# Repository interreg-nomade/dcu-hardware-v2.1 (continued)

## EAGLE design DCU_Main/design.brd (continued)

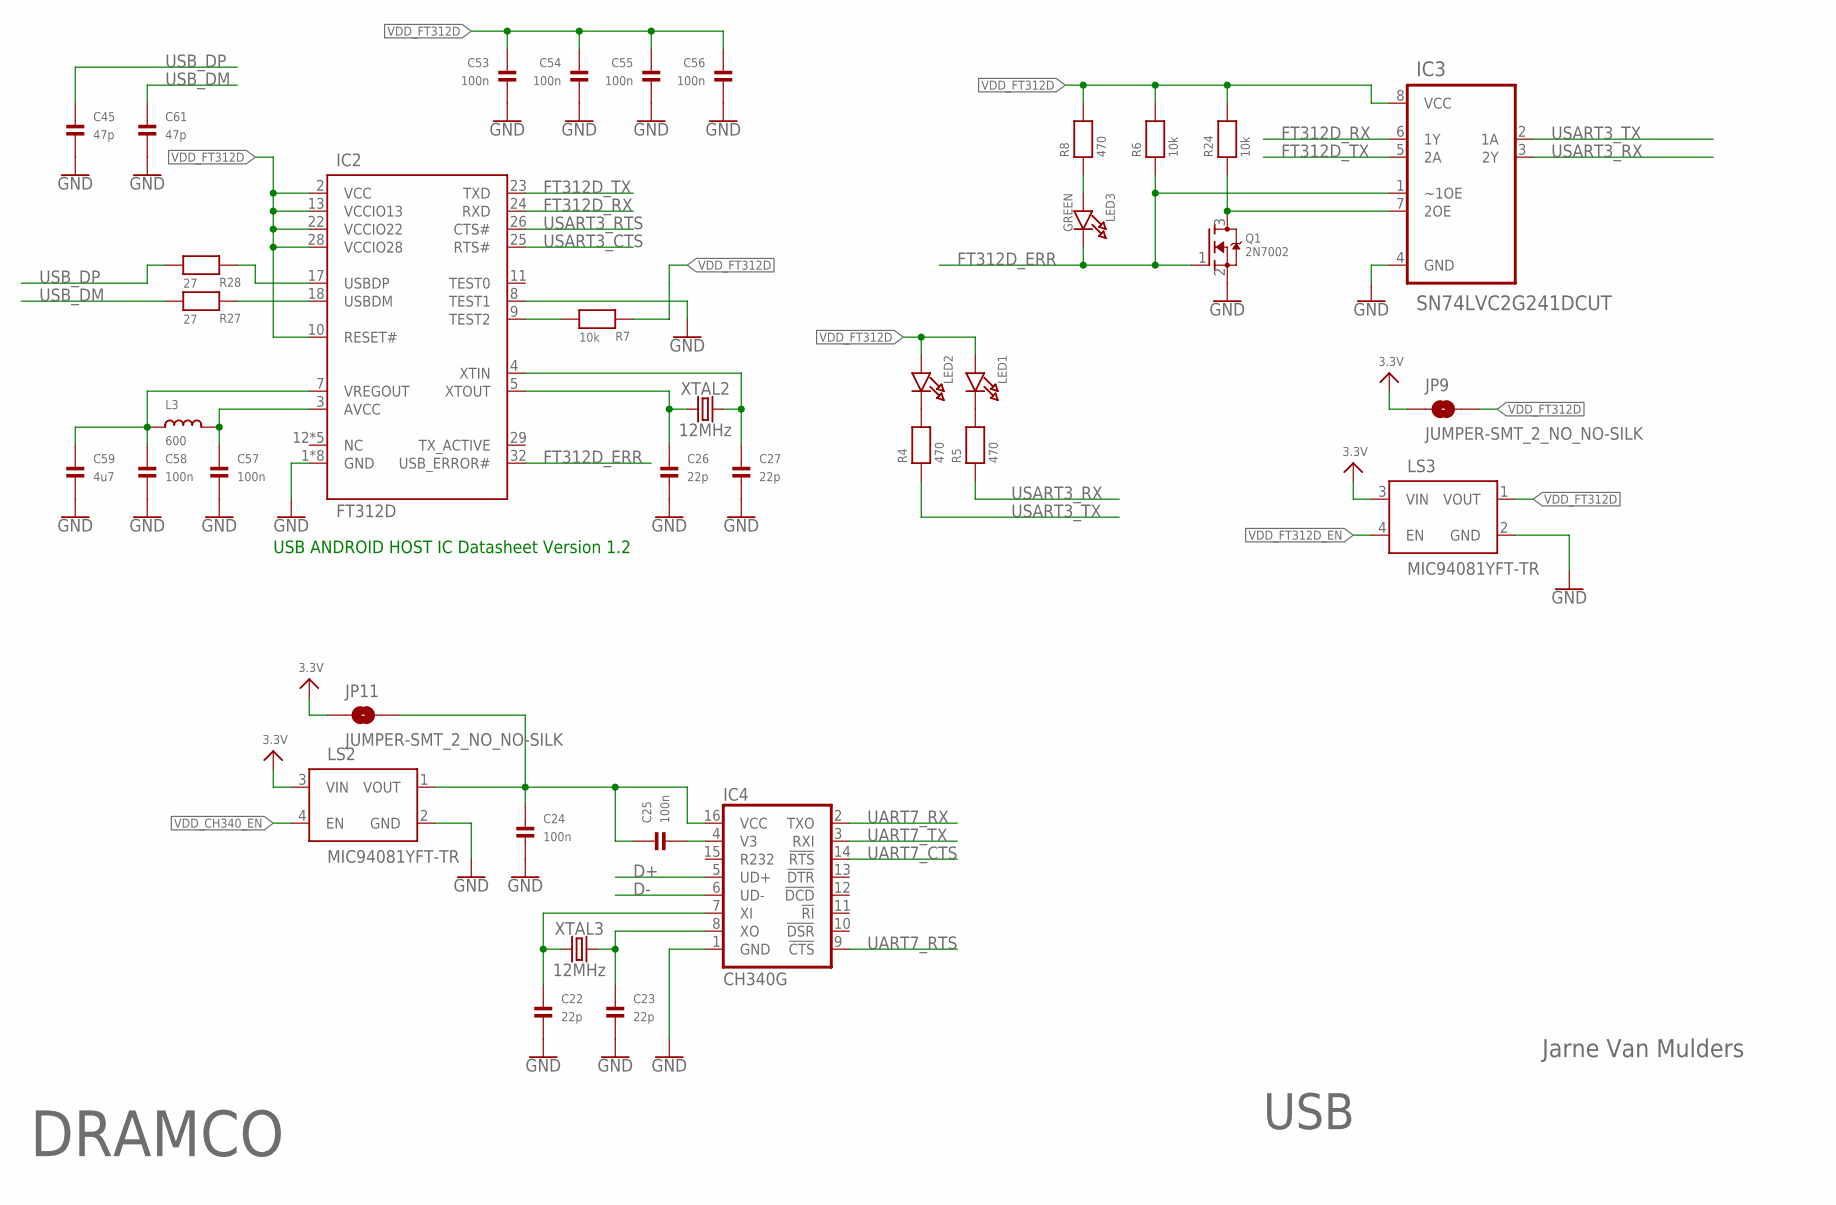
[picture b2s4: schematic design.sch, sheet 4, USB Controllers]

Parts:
C22, C23, C26, C27: 22p; 0603
C24, C25, C53, C54, C55, C56, C57, C58: 100n; 0603
C45, C61: 47p; 0603
C59: 4u7; 0603
IC2: FT312D; QFP80P900X900X160-32N
IC3: SN74LVC2G241DCUT; SOP50P310X90-8N
IC4: CH340G; SO016
JP9, JP11: JUMPER-SMT_2_NO_NO-SILK; SMT-JUMPER_2_NO_NO-SILK
L3: 600; 0603
LED1, LED2: LED0805; CHIPLED_0805
LED3: GREEN; CHIPLED_0805
LS2, LS3: MIC94081YFT-TR; IC_MIC94081YFT-TR
Q1: 2N7002; SOT23-WIDE
R4, R5, R8: 470; 0603
R6, R7, R24: 10k; 0603
R27, R28: 27; 0603
XTAL2, XTAL3: 12MHz; CRYSTAL-SMD-3.2X2.5MM

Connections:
3.3V: JP9.1, JP11.1, LS2.3 (VIN), LS3.3 (VIN); also elsewhere on the board
D+: IC4.5 (UD+); also elsewhere on the board
D-: IC4.6 (UD-); also elsewhere on the board
FT312D_ERR: IC2.32 (USB_ERROR#), IC3.1 (~1OE), LED3.C, Q1.1 (G), R6.1; also elsewhere on the board
FT312D_RX: IC2.24 (RXD), IC3.6 (1Y)
FT312D_TX: IC2.23 (TXD), IC3.5 (2A)
GND: C22.2, C23.2, C24.2, C26.2, C27.2, C45.2, C53.2, C54.2, C55.2, C56.2, C57.2, C58.2, C59.2, C61.2, IC2.1 (GND), IC2.6 (GND), IC2.8 (TEST1), IC2.14 (GND), IC2.15 (GND), IC2.16 (GND), IC2.19 (GND), IC2.27 (GND), IC2.33 (GND), IC3.4 (GND), IC4.1 (GND), LS2.2 (GND), LS3.2 (GND), Q1.2 (S); also elsewhere on the board
unnamed: LED2.C, R4.2
unnamed: LED1.C, R5.2
unnamed: C27.1, IC2.4 (XTIN), XTAL2.3 (2)
unnamed: C26.1, IC2.5 (XTOUT), XTAL2.1
unnamed: C24.1, C25.1, IC4.16 (VCC), JP11.2, LS2.1 (VOUT)
unnamed: LED3.A, R8.1
unnamed: IC2.9 (TEST2), R7.1
unnamed: IC3.7 (2OE), Q1.3 (D), R24.1
unnamed: C22.1, IC4.7 (XI), XTAL3.1
unnamed: C23.1, IC4.8 (XO), XTAL3.3 (2)
unnamed: C25.2, IC4.4 (V3)
unnamed: C58.1, C59.1, IC2.7 (VREGOUT), L3.1
unnamed: C57.1, IC2.3 (AVCC), L3.2
unnamed: IC2.18 (USBDM), R27.2
unnamed: IC2.17 (USBDP), R28.2
UART7_CTS: IC4.14 (!RTS); also elsewhere on the board
UART7_RTS: IC4.9 (!CTS); also elsewhere on the board
UART7_RX: IC4.2 (TXO); also elsewhere on the board
UART7_TX: IC4.3 (RXI); also elsewhere on the board
USART3_CTS: IC2.25 (RTS#); also elsewhere on the board
USART3_RTS: IC2.26 (CTS#); also elsewhere on the board
USART3_RX: IC3.3 (2Y), R5.1; also elsewhere on the board
USART3_TX: IC3.2 (1A), R4.1; also elsewhere on the board
USB_DM: C61.1, R27.1; also elsewhere on the board
USB_DP: C45.1, R28.1; also elsewhere on the board
VDD_CH340_EN: LS2.4 (EN); also elsewhere on the board
VDD_FT312D: C53.1, C54.1, C55.1, C56.1, IC2.2 (VCC), IC2.10 (RESET#), IC2.13 (VCCIO13), IC2.22 (VCCIO22), IC2.28 (VCCIO28), IC3.8 (VCC), JP9.2, LED1.A, LED2.A, LS3.1 (VOUT), R6.2, R7.2, R8.2, R24.2
VDD_FT312D_EN: LS3.4 (EN); also elsewhere on the board

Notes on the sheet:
USB ANDROID HOST IC Datasheet Version 1.2
USB
Jarne Van Mulders
DRAMCO

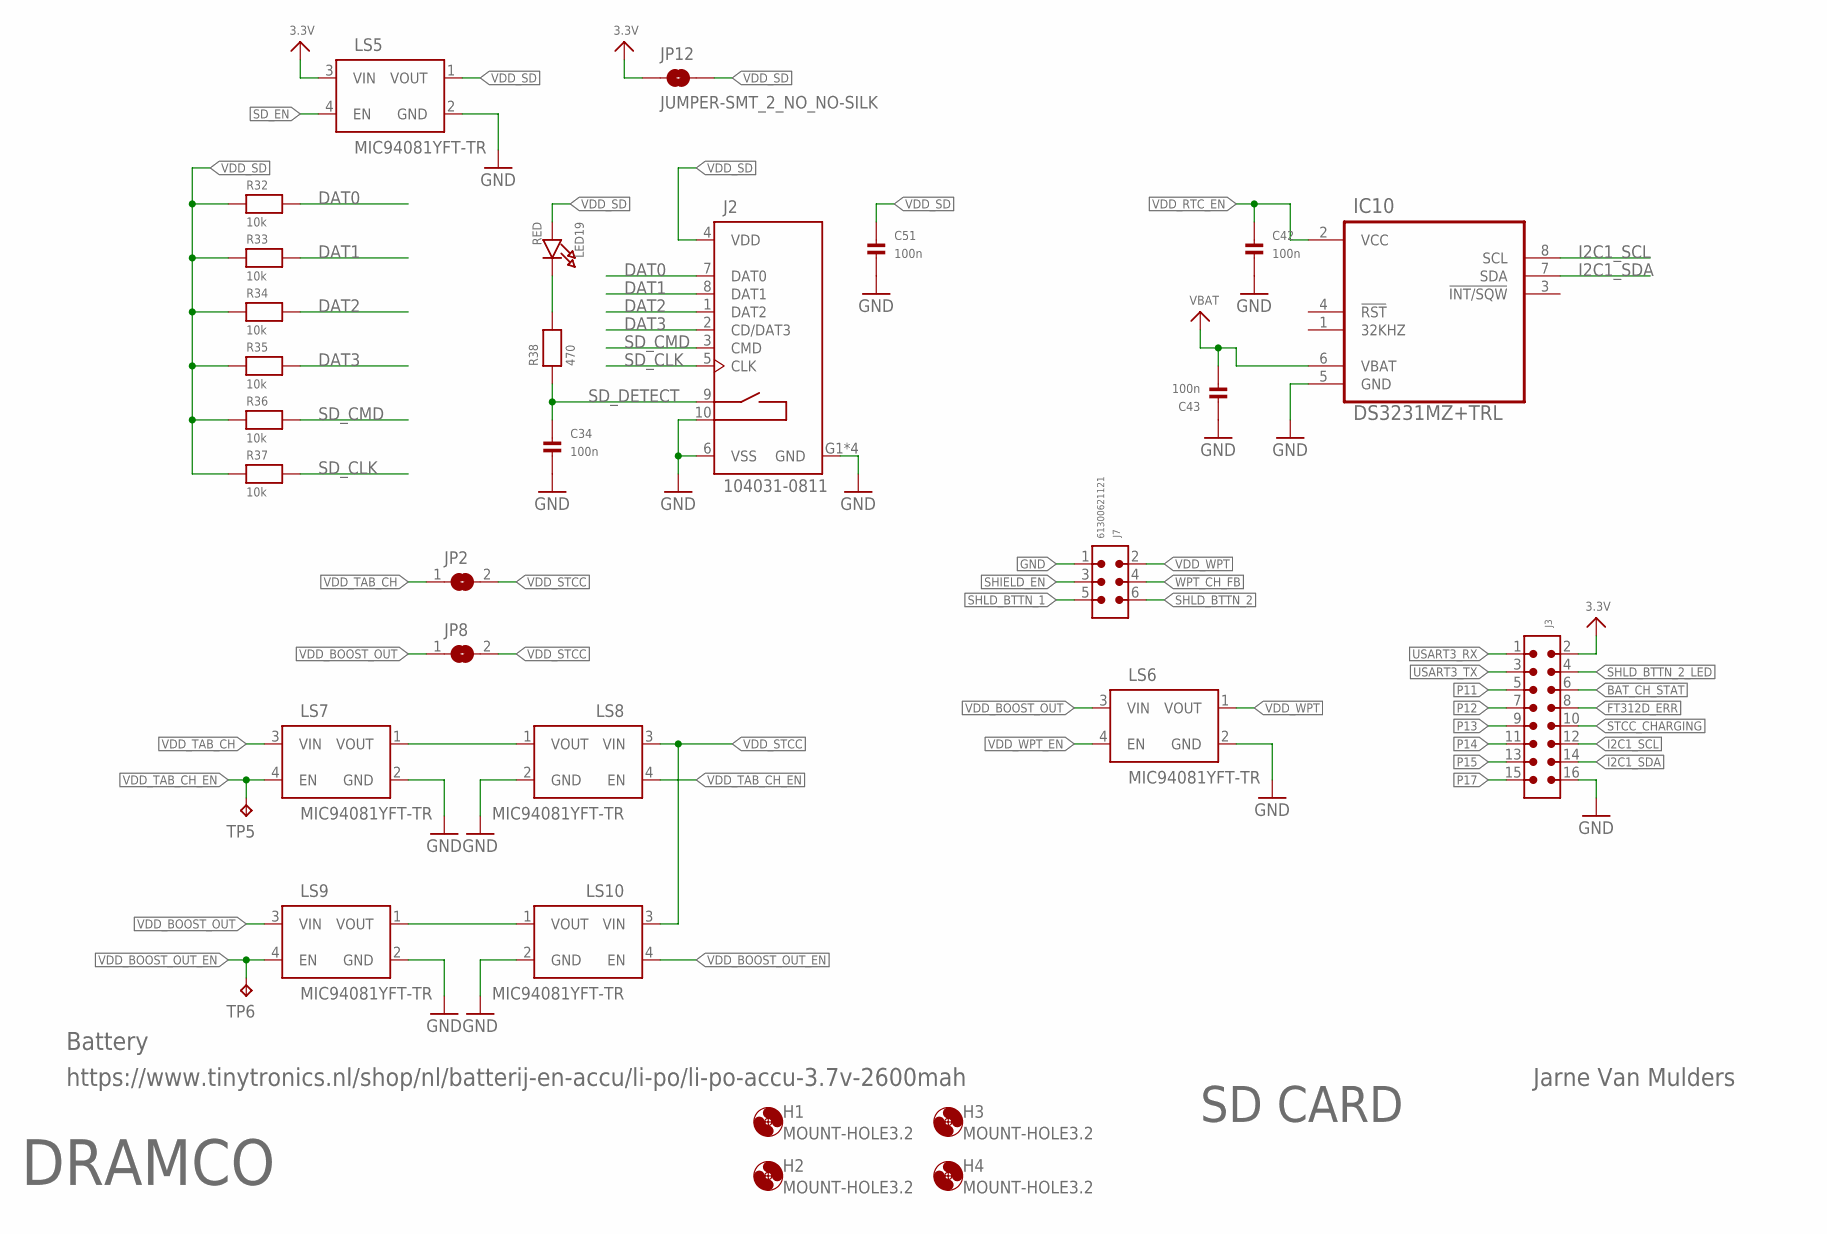
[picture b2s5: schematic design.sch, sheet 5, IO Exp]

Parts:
C34, C42, C43, C51: 100n; 0603
H1, H2, H3, H4: MOUNT-HOLE3.2; 3,2
IC10: DS3231MZ+TRL; SOIC127P600X175-8N
J2: 104031-0811; MOLEX_104031-0811
J3: 6130XX21121_61301621121; 61301621121
J7: 61300621121
JP2, JP8: SOLDERJUMPERREFLOW; SOLDERJUMPER_REFLOW
JP12: JUMPER-SMT_2_NO_NO-SILK; SMT-JUMPER_2_NO_NO-SILK
LED19: RED; CHIPLED_0805
LS5, LS6, LS7, LS8, LS9, LS10: MIC94081YFT-TR; IC_MIC94081YFT-TR
R32, R33, R34, R35, R36, R37: 10k; 0603
R38: 470; 0603
TP5, TP6: TPTP10R; TP10R

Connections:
3.3V: J3.2, JP12.1, LS5.3 (VIN); also elsewhere on the board
BAT_CH_STAT: J3.6; also elsewhere on the board
DAT0: J2.7 (DAT0), R32.2; also elsewhere on the board
DAT1: J2.8 (DAT1), R33.2; also elsewhere on the board
DAT2: J2.1 (DAT2), R34.2; also elsewhere on the board
DAT3: J2.2 (CD/DAT3), R35.2; also elsewhere on the board
FT312D_ERR: J3.8; also elsewhere on the board
GND: C34.2, C42.2, C43.1, C51.2, IC10.5 (GND), J2.6 (VSS), J2.10 (CARD_DET2), J2.G1 (GND), J2.G2 (GND), J2.G3 (GND), J2.G4 (GND), J3.16, J7.1, LS5.2 (GND), LS6.2 (GND), LS7.2 (GND), LS8.2 (GND), LS9.2 (GND), LS10.2 (GND); also elsewhere on the board
I2C1_SCL: IC10.8 (SCL), J3.12; also elsewhere on the board
I2C1_SDA: IC10.7 (SDA), J3.14; also elsewhere on the board
unnamed: LED19.C, R38.2
unnamed: LS9.1 (VOUT), LS10.1 (VOUT)
unnamed: LS7.1 (VOUT), LS8.1 (VOUT)
P11: J3.5; also elsewhere on the board
P12: J3.7; also elsewhere on the board
P13: J3.9; also elsewhere on the board
P14: J3.11; also elsewhere on the board
P15: J3.13; also elsewhere on the board
P17: J3.15; also elsewhere on the board
SD_CLK: J2.5 (CLK), R37.2; also elsewhere on the board
SD_CMD: J2.3 (CMD), R36.2; also elsewhere on the board
SD_DETECT: C34.1, J2.9 (CARD_DET1), R38.1; also elsewhere on the board
SD_EN: LS5.4 (EN); also elsewhere on the board
SHIELD_EN: J7.3; also elsewhere on the board
SHLD_BTTN_1: J7.5; also elsewhere on the board
SHLD_BTTN_2: J7.6; also elsewhere on the board
SHLD_BTTN_2_LED: J3.4; also elsewhere on the board
STCC_CHARGING: J3.10; also elsewhere on the board
USART3_RX: J3.1; also elsewhere on the board
USART3_TX: J3.3; also elsewhere on the board
VBAT: C43.2, IC10.6 (VBAT); also elsewhere on the board
VDD_BOOST_OUT: JP8.1, LS6.3 (VIN), LS9.3 (VIN); also elsewhere on the board
VDD_BOOST_OUT_EN: LS9.4 (EN), LS10.4 (EN), TP6.TP; also elsewhere on the board
VDD_RTC_EN: C42.1, IC10.2 (VCC); also elsewhere on the board
VDD_SD: C51.1, J2.4 (VDD), JP12.2, LED19.A, LS5.1 (VOUT), R32.1, R33.1, R34.1, R35.1, R36.1, R37.1
VDD_STCC: JP2.2, JP8.2, LS8.3 (VIN), LS10.3 (VIN); also elsewhere on the board
VDD_TAB_CH: JP2.1, LS7.3 (VIN); also elsewhere on the board
VDD_TAB_CH_EN: LS7.4 (EN), LS8.4 (EN), TP5.TP; also elsewhere on the board
VDD_WPT: J7.2, LS6.1 (VOUT)
VDD_WPT_EN: LS6.4 (EN); also elsewhere on the board
WPT_CH_FB: J7.4; also elsewhere on the board

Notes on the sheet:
Jarne Van Mulders
DRAMCO
SD CARD
Battery
https://www.tinytronics.nl/shop/nl/batterij-en-accu/li-po/li-po-accu-3.7v-2600mah

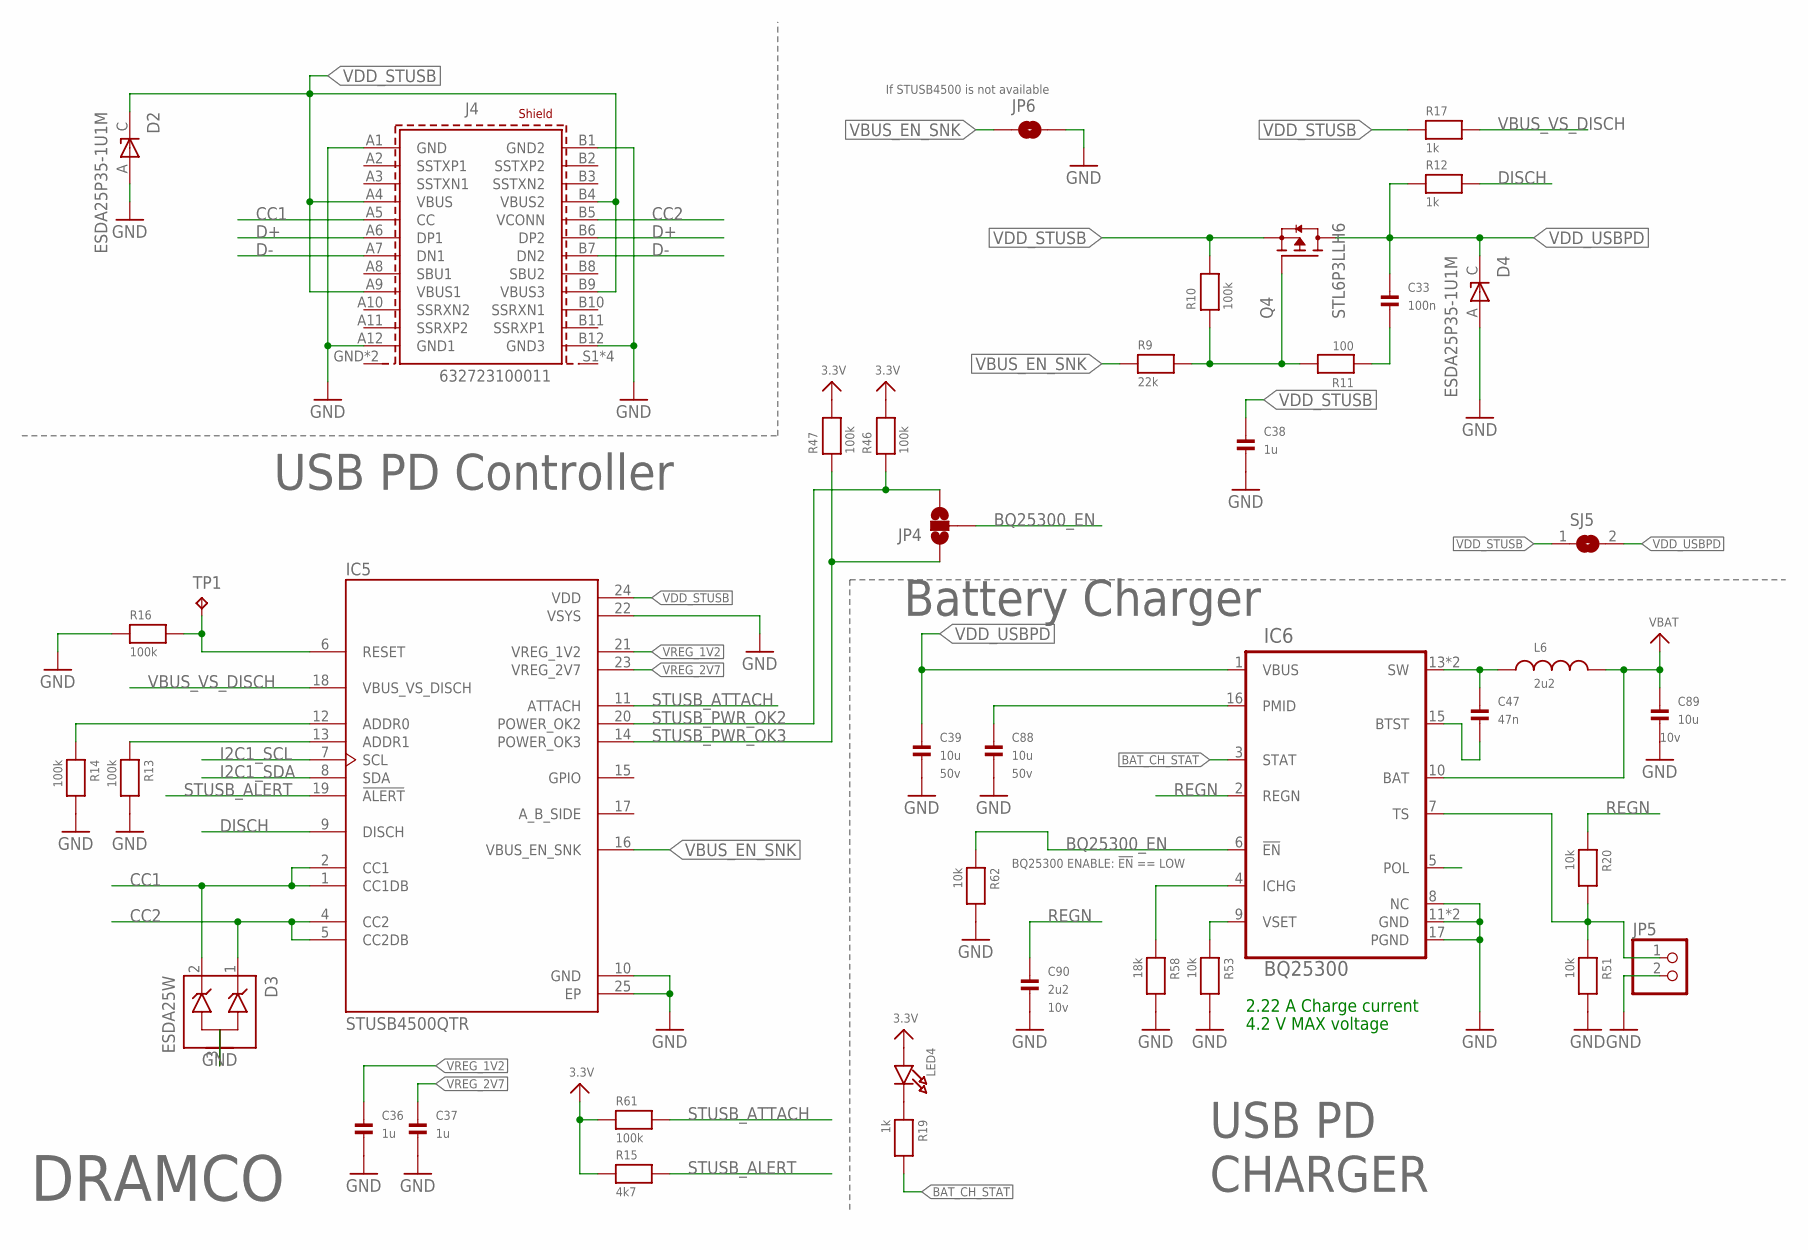
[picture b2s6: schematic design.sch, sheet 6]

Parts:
C33: 100n; 0603
C36, C37: 1u; 0603
C38: 1u; 0805
C39, C88: 10u; 1206
C47: 47n; 0603
C89: 10u; 0805
C90: 2u2; 0603
D2, D4: ESDA25P35-1U1M; TVS_ESDA25P35-1U1M
D3: ESDA25W; SOT65P210X110-3N
IC5: STUSB4500QTR; QFN50P400X400X90-25N
IC6: BQ25300; QFN50P350X350X100-21N
J4: 632723100011
JP4: JUMPER-SMT_3_NO_NO-SILK; SMT-JUMPER_3_NO_NO-SILK
JP5: HEADER-1X2ROUND; 1X02_ROUND
JP6: JUMPER-SMT_2_NO_NO-SILK; SMT-JUMPER_2_NO_NO-SILK
L6: 2u2; WE-MAIA_3020
LED4: LED0805; CHIPLED_0805
Q4: STL6P3LLH6; TRANS_STL6P3LLH6
R9: 22k; 0603
R10, R13, R14, R16, R46, R47, R61: 100k; 0603
R11: 100; 0603
R12, R17, R19: 1k; 0603
R15: 4k7; 0603
R20, R51, R53, R62: 10k; 0603
R58: 18k; 0603
SJ5: SOLDERJUMPERREFLOW; SOLDERJUMPER_REFLOW
TP1: TPTP10R; TP10R

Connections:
3.3V: LED4.A, R15.1, R46.2, R47.2, R61.1; also elsewhere on the board
BAT_CH_STAT: IC6.3 (STAT), R19.2; also elsewhere on the board
BQ25300_EN: IC6.6 (!EN), JP4.2, R62.1; also elsewhere on the board
CC1: D3.2 (C2), IC5.1 (CC1DB), IC5.2 (CC1), J4.A5 (CC)
CC2: D3.1 (C1), IC5.4 (CC2), IC5.5 (CC2DB), J4.B5 (VCONN)
D+: J4.A6 (DP1), J4.B6 (DP2); also elsewhere on the board
D-: J4.A7 (DN1), J4.B7 (DN2); also elsewhere on the board
DISCH: IC5.9 (DISCH), R12.2
GND: C36.2, C37.2, C38.2, C39.2, C88.2, C89.2, C90.2, D2.A, D3.3 (CA), D4.A, IC5.10 (GND), IC5.22 (VSYS), IC5.25 (EP), IC6.8 (NC), IC6.11 (GND), IC6.12 (GND), IC6.17 (PGND), J4.A1 (GND), J4.A12 (GND1), J4.B1 (GND2), J4.B12 (GND3), JP5.2, JP6.2, R13.2, R14.2, R16.1, R51.2, R53.2, R58.2, R62.2; also elsewhere on the board
I2C1_SCL: IC5.7 (SCL); also elsewhere on the board
I2C1_SDA: IC5.8 (SDA); also elsewhere on the board
unnamed: IC5.13 (ADDR1), R13.1
unnamed: C33.2, R11.1
unnamed: Q4.4 (G), R9.2, R10.1, R11.2
unnamed: IC5.12 (ADDR0), R14.1
unnamed: IC5.6 (RESET), R16.2, TP1.TP
unnamed: IC6.9 (VSET), R53.1
unnamed: IC6.4 (ICHG), R58.1
unnamed: LED4.C, R19.1
unnamed: C47.2, IC6.15 (BTST)
unnamed: C88.1, IC6.16 (PMID)
unnamed: C47.1, IC6.13 (SW), IC6.14 (SW), L6.1
unnamed: IC6.7 (TS), JP5.1, R20.2, R51.1
REGN: C90.1, IC6.2 (REGN), R20.1
STUSB_ALERT: IC5.19 (!ALERT), R15.2; also elsewhere on the board
STUSB_ATTACH: IC5.11 (ATTACH), R61.2; also elsewhere on the board
STUSB_PWR_OK2: IC5.20 (POWER_OK2), JP4.3, R46.1; also elsewhere on the board
STUSB_PWR_OK3: IC5.14 (POWER_OK3), JP4.1, R47.1; also elsewhere on the board
VBAT: C89.1, IC6.10 (BAT), L6.2; also elsewhere on the board
VBUS_EN_SNK: IC5.16 (VBUS_EN_SNK), JP6.1, R9.1
VBUS_VS_DISCH: IC5.18 (VBUS_VS_DISCH), R17.2
VDD_STUSB: C38.1, D2.C, IC5.24 (VDD), J4.A4 (VBUS), J4.A9 (VBUS1), J4.B4 (VBUS2), J4.B9 (VBUS3), Q4.1 (S), Q4.2 (S), Q4.3 (S), R10.2, R17.1, SJ5.1
VDD_USBPD: C33.1, C39.1, D4.C, IC6.1 (VBUS), Q4.5_8 (D), R12.1, SJ5.2; also elsewhere on the board
VREG_1V2: C36.1, IC5.21 (VREG_1V2)
VREG_2V7: C37.1, IC5.23 (VREG_2V7)

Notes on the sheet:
DRAMCO
50v
BQ25300 ENABLE: !EN! == LOW
10v
USB PD CHARGER
2.22 A Charge current
4.2 V MAX voltage
USB PD Controller
Battery Charger
If STUSB4500 is not available

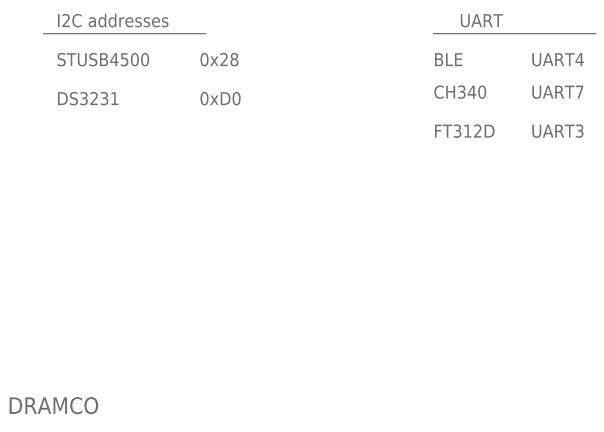
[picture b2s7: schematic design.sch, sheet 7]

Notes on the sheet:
DRAMCO
I2C addresses
STUSB4500
DS3231
0x28
0xD0
UART
UART4
BLE
CH340
UART7
UART3
FT312D

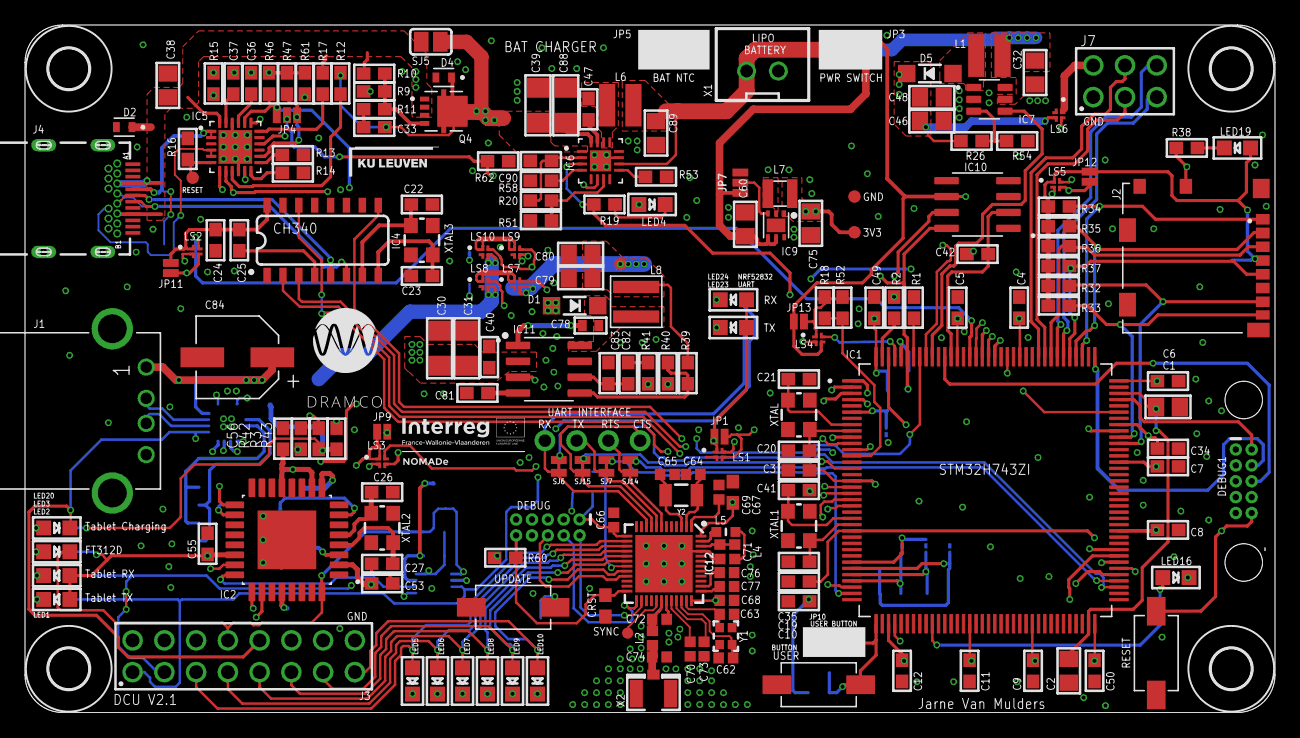
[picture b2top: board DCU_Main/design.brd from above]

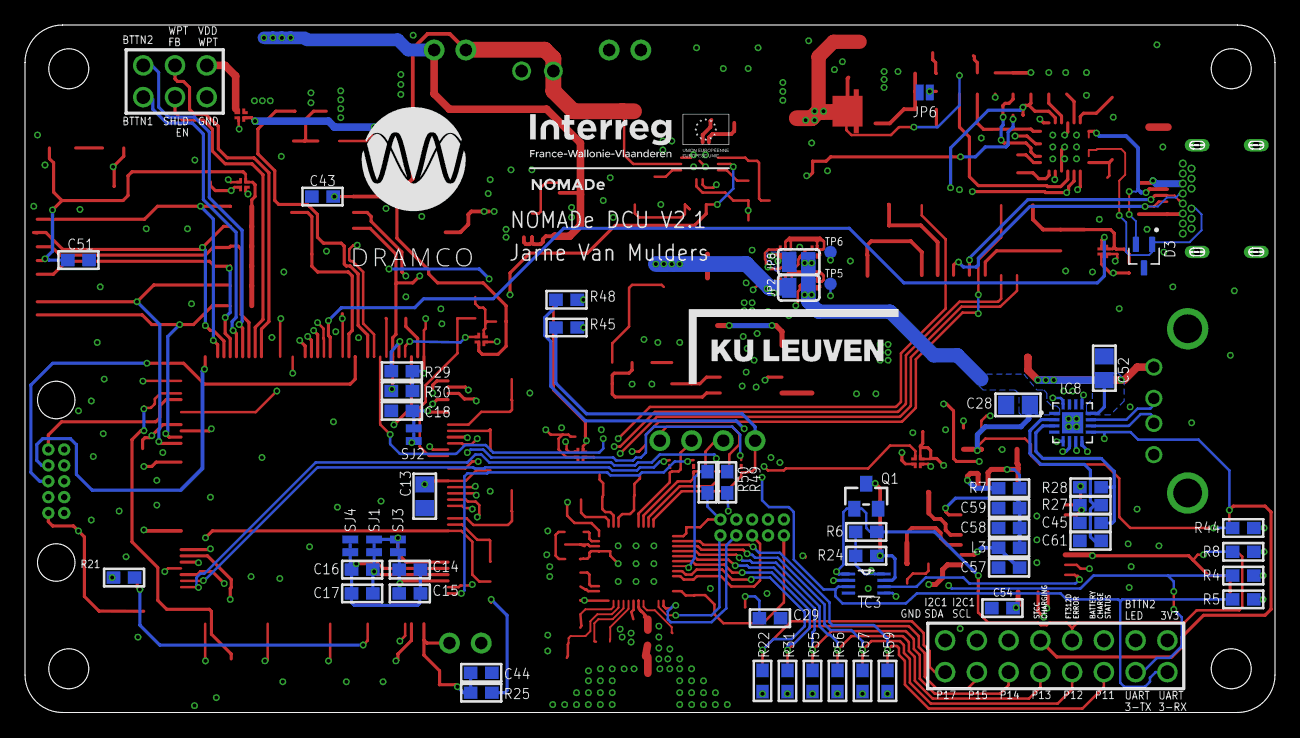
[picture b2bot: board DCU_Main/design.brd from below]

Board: 4 copper layers, 99.9 x 54.9 mm, 253 parts (55 on the bottom side), 179 nets.
